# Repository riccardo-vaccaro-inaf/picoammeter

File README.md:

# picoammeter
Repo for the picoammeter part of the LP board

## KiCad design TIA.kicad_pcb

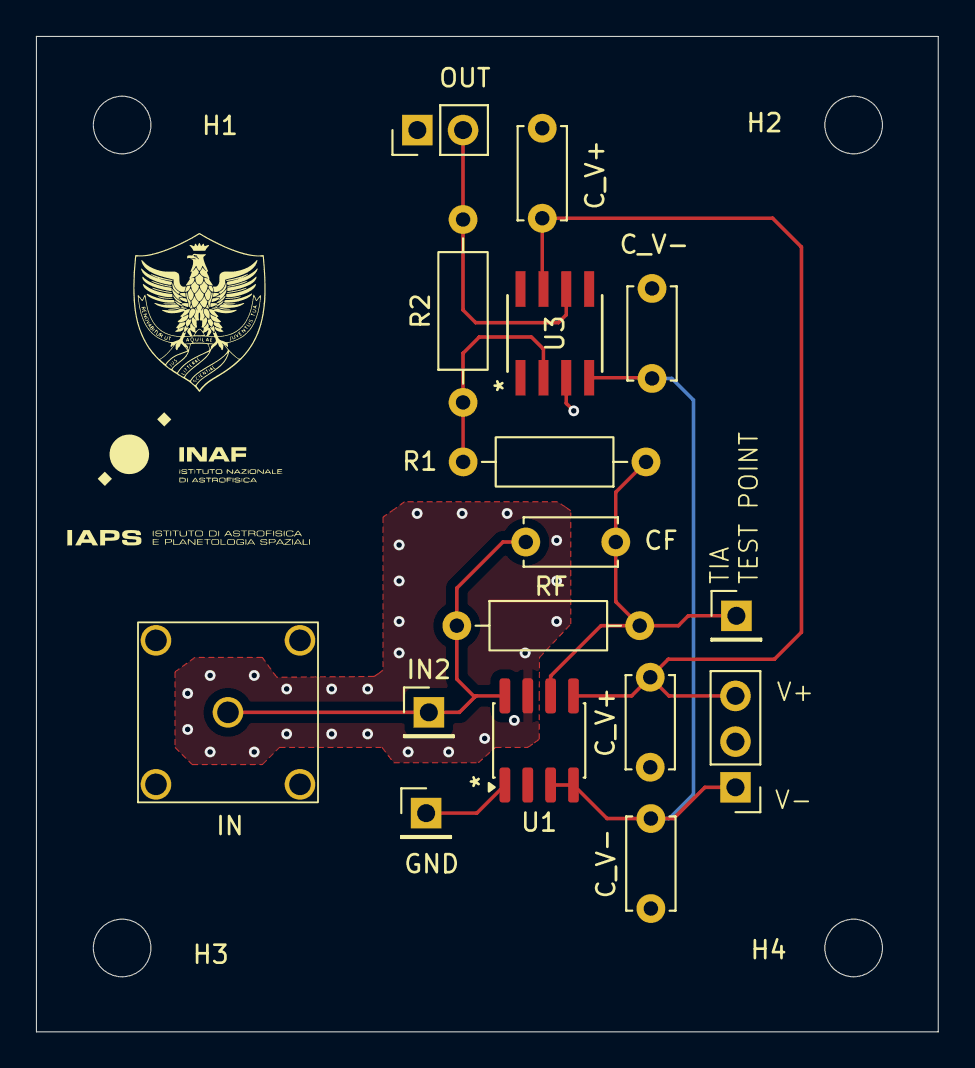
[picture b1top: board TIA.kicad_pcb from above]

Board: 2 copper layers, 50.1 x 55.3 mm, 20 parts (0 on the bottom side), 7 nets.

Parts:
CF: C; C_Disc_D5.0mm_W2.5mm_P5.00mm
C_V+: C; C_Disc_D5.0mm_W2.5mm_P5.00mm
C_V+#2: C; C_Disc_D5.0mm_W2.5mm_P5.00mm
C_V-: C; C_Disc_D5.0mm_W2.5mm_P5.00mm
C_V-#2: C; C_Disc_D5.0mm_W2.5mm_P5.00mm
GND: Conn_01x01_Pin; PinHeader_1x01_P2.54mm_Vertical
H1, H2, H3, H4: MountingHole; MountingHole_3.2mm_M3
IN: Conn_Coaxial; BNC_10x10
IN2: Conn_01x01_Pin; PinHeader_1x01_P2.54mm_Vertical
J1: Conn_01x03_Pin; PinHeader_1x03_P2.54mm_Vertical
OUT: Conn_01x02_Pin; PinHeader_1x02_P2.54mm_Vertical
R1: 1k; R_Axial_DIN0207_L6.3mm_D2.5mm_P10.16mm_Horizontal
R2: 220k; R_Axial_DIN0207_L6.3mm_D2.5mm_P10.16mm_Horizontal
RF: 10M; R_Axial_DIN0207_L6.3mm_D2.5mm_P10.16mm_Horizontal
TIA TEST  POINT: Conn_01x01_Pin; PinHeader_1x01_P2.54mm_Vertical
U1: ADA4530-1; SOIC-8_3.9x4.9mm_P1.27mm
U3: AD8628ARZ-REEL; R_8_ADI

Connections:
GND: C_V+.1, C_V+#2.2, C_V-.1, C_V-#2.2, GND.1, IN.2 (Ext), J1.2, OUT.1, U1.1 (+), U3.3 (+IN)
unnamed: C_V-.2, C_V-#2.1, J1.1, U1.3 (IC), U1.4 (V-), U3.4 (V-)
unnamed: C_V+.2, C_V+#2.1, J1.3, U1.5 (V+), U3.7 (V+)
unnamed: CF.1, IN.1 (In), IN2.1, RF.1, U1.8 (-)
unnamed: OUT.2, R2.2, U3.6 (OUT)
unnamed: CF.2, R1.1, RF.2, TIA TEST POINT.1, U1.6
unnamed: R1.2, R2.1, U3.2 (-IN)

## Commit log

2026-03-17 File base del progetto
